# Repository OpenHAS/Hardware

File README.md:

# Hardware
Hardware modules for the OpenHAS project

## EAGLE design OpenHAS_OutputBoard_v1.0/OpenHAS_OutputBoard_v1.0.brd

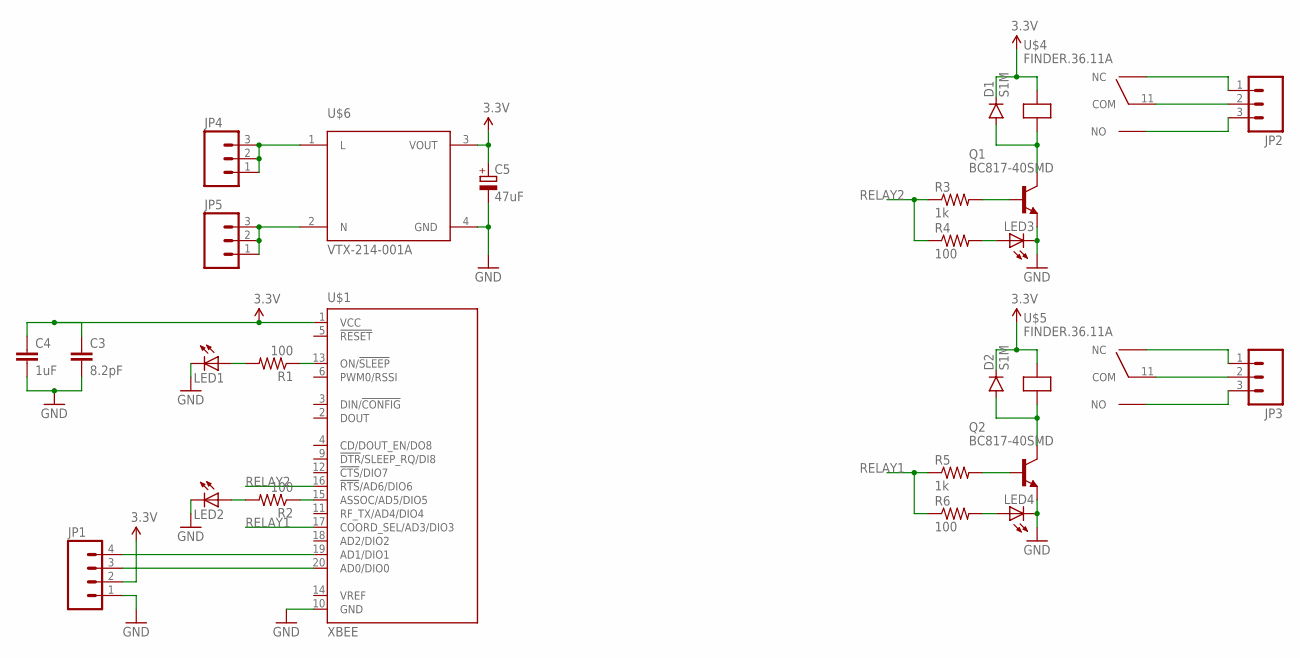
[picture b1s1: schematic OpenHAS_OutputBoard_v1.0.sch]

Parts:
C3: 8.2pF; 0805
C4: 1uF; 0805
C5: 47uF; E2-5
D1, D2: S1M; SMA-DIODE
JP1: M04SCREW; SCREWTERMINAL-3.5MM-4
JP2, JP3, JP4, JP5: M03-SCREW-5MM; SCREWTERMINAL-5MM-3
LED1, LED2, LED3, LED4: LEDCHIP-LED0805; CHIP-LED0805
Q1, Q2: BC817-40SMD; SOT23-BEC
R1, R2, R4, R6: 100; 0805
R3, R5: 1k; 0805
U$1: XBEE
U$4, U$5: FINDER.36.11A; 31.11
U$6: VTX-214-001A; VTX-214-003-X

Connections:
3.3V: C3.1, C4.1, C5.+, D1.C, D2.C, JP1.2, U$1.1 (VCC), U$4.A1, U$5.A1, U$6.3 (VOUT)
GND: C3.2, C4.2, C5.-, JP1.1, LED1.C, LED2.C, LED3.C, LED4.C, Q1.E, Q2.E, U$1.10 (GND), U$6.4 (GND)
unnamed: LED2.A, R2.2
unnamed: D1.A, Q1.C, U$4.A2
unnamed: LED3.A, R4.2
unnamed: JP2.2, U$4.11 (COM)
unnamed: LED1.A, R1.2
unnamed: Q1.B, R3.2
unnamed: JP2.3, U$4.14 (NO)
unnamed: JP2.1, U$4.12 (NC)
unnamed: JP3.2, U$5.11 (COM)
unnamed: JP5.1, JP5.2, JP5.3, U$6.2 (N)
unnamed: JP4.1, JP4.2, JP4.3, U$6.1 (L)
unnamed: D2.A, Q2.C, U$5.A2
unnamed: Q2.B, R5.2
unnamed: LED4.A, R6.2
unnamed: JP3.3, U$5.14 (NO)
unnamed: JP3.1, U$5.12 (NC)
unnamed: R2.1, U$1.15 (ASSOC/AD5/DIO5)
unnamed: R1.1, U$1.13 (ON/!SLEEP)
unnamed: JP1.3, U$1.20 (AD0/DIO0)
unnamed: JP1.4, U$1.19 (AD1/DIO1)
RELAY1: R5.1, R6.1, U$1.17 (COORD_SEL/AD3/DIO3)
RELAY2: R3.1, R4.1, U$1.16 (!RTS!/AD6/DIO6)

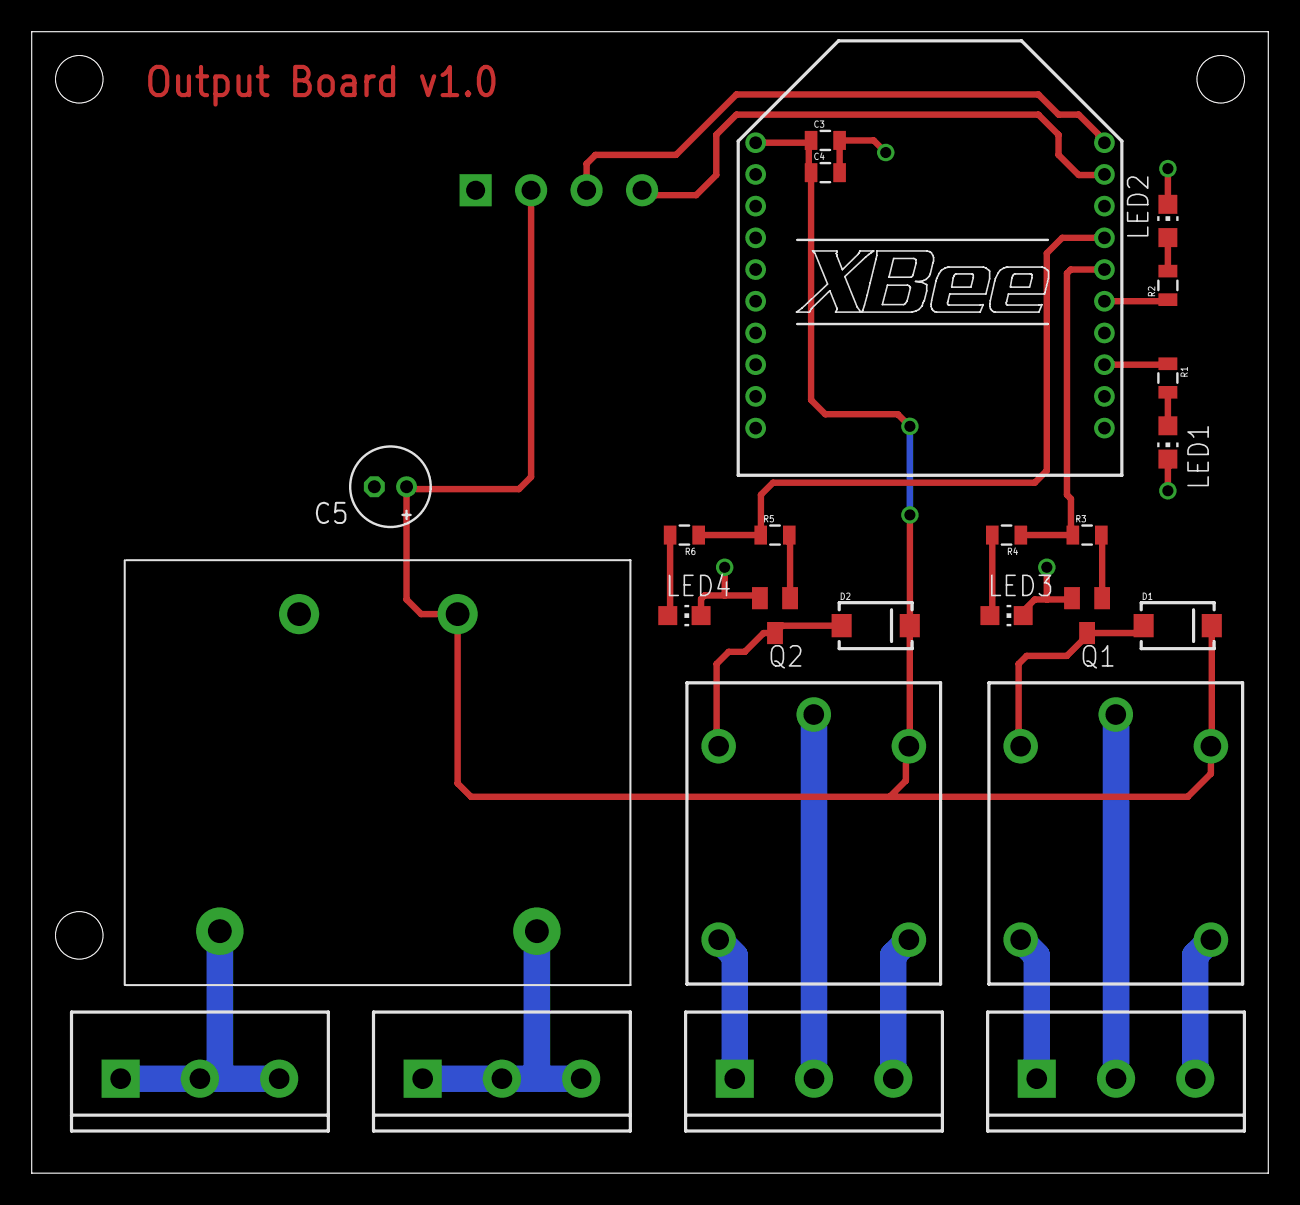
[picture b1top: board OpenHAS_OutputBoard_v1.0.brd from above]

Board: 2 copper layers, 78.0 x 72.0 mm, 26 parts (1 on the bottom side), 24 nets.

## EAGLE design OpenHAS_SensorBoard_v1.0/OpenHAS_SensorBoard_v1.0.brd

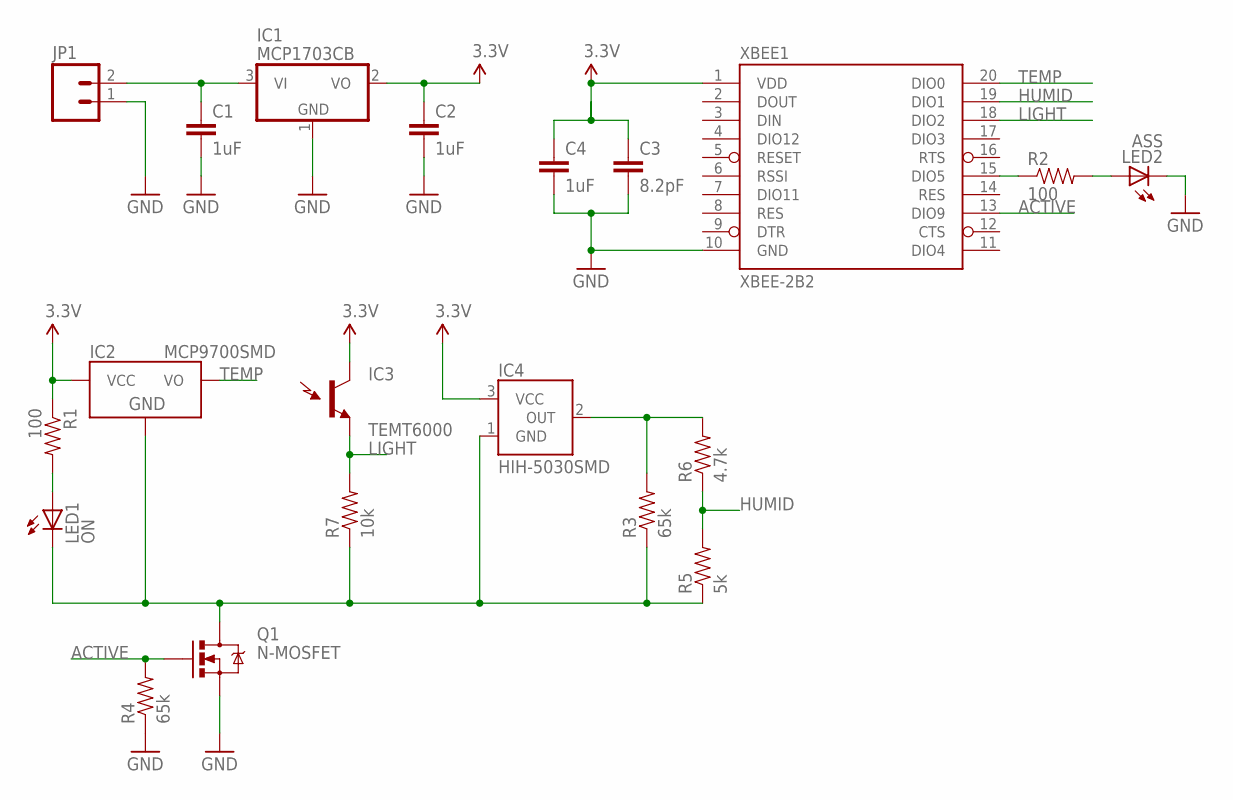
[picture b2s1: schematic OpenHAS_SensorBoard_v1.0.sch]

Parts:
C1, C2, C4: 1uF; 0805
C3: 8.2pF; 0805
IC1: MCP1703CB; SOT23
IC2: MCP9700SMD; SOT23-3
IC3: TEMT6000; TEMT6000-SEN
IC4: HIH-5030SMD; HIH-4030
JP1: M02POLAR; MOLEX-1X2
LED1: ON; CHIP-LED0805
LED2: ASS; CHIP-LED0805
Q1: N-MOSFET; SOT23-3
R1, R2: 100; 0805
R3, R4: 65k; 0805
R5: 5k; 0805
R6: 4.7k; 0805
R7: 10k; 0805
XBEE1: XBEE-2B2; XBEE-SILK

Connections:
3.3V: C2.1, C3.1, C4.1, IC1.2 (VO), IC2.1 (VCC), IC3.COLLECTOR (C1), IC4.3 (VCC), R1.1, XBEE1.1 (VDD)
ACTIVE: Q1.1 (G), R4.2, XBEE1.13 (DIO9)
GND: C1.2, C2.2, C3.2, C4.2, IC1.1 (GND), JP1.1, LED2.C, Q1.2 (S), R4.1, XBEE1.10 (GND)
HUMID: R5.2, R6.1, XBEE1.19 (DIO1)
LIGHT: IC3.EMITTER (E1), R7.2, XBEE1.18 (DIO2)
unnamed: R2.1, XBEE1.15 (DIO5)
unnamed: LED2.A, R2.2
unnamed: IC4.2 (OUT), R3.2, R6.2
unnamed: LED1.A, R1.2
RAW: C1.1, IC1.3 (VI), JP1.2
SW_GND: IC2.3 (GND), IC4.1 (GND), LED1.C, Q1.3 (D), R3.1, R5.1, R7.1
TEMP: IC2.2 (VO), XBEE1.20 (DIO0)

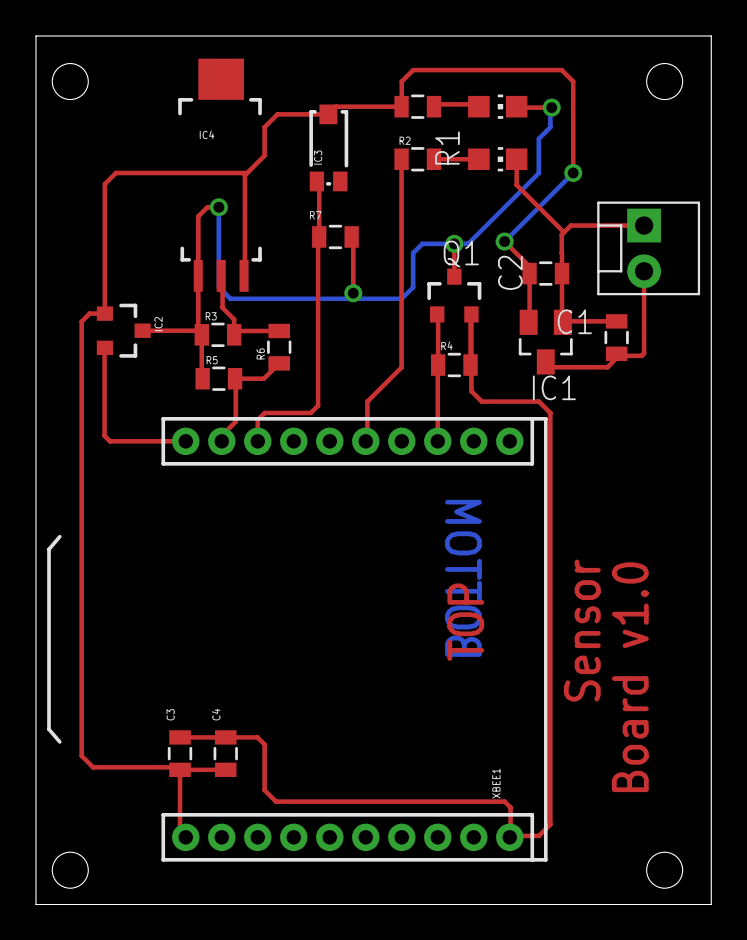
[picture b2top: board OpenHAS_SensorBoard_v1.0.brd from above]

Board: 2 copper layers, 37.5 x 48.2 mm, 20 parts (0 on the bottom side), 12 nets.

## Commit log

2016-03-10 Adding the sensor board to the project.
2016-03-10 Added voltage divider to the humidity sensor. Redesigned layout
2016-03-10 Adding the output board to the repo

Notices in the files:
parts and their libraries:
SparkFun-Passives: Licensing: Creative Commons ShareAlike 4.0 International - https://creativecommons.org/licenses/by-sa/4.0
